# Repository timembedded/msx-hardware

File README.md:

# msx-hardware
MSX hardware related things

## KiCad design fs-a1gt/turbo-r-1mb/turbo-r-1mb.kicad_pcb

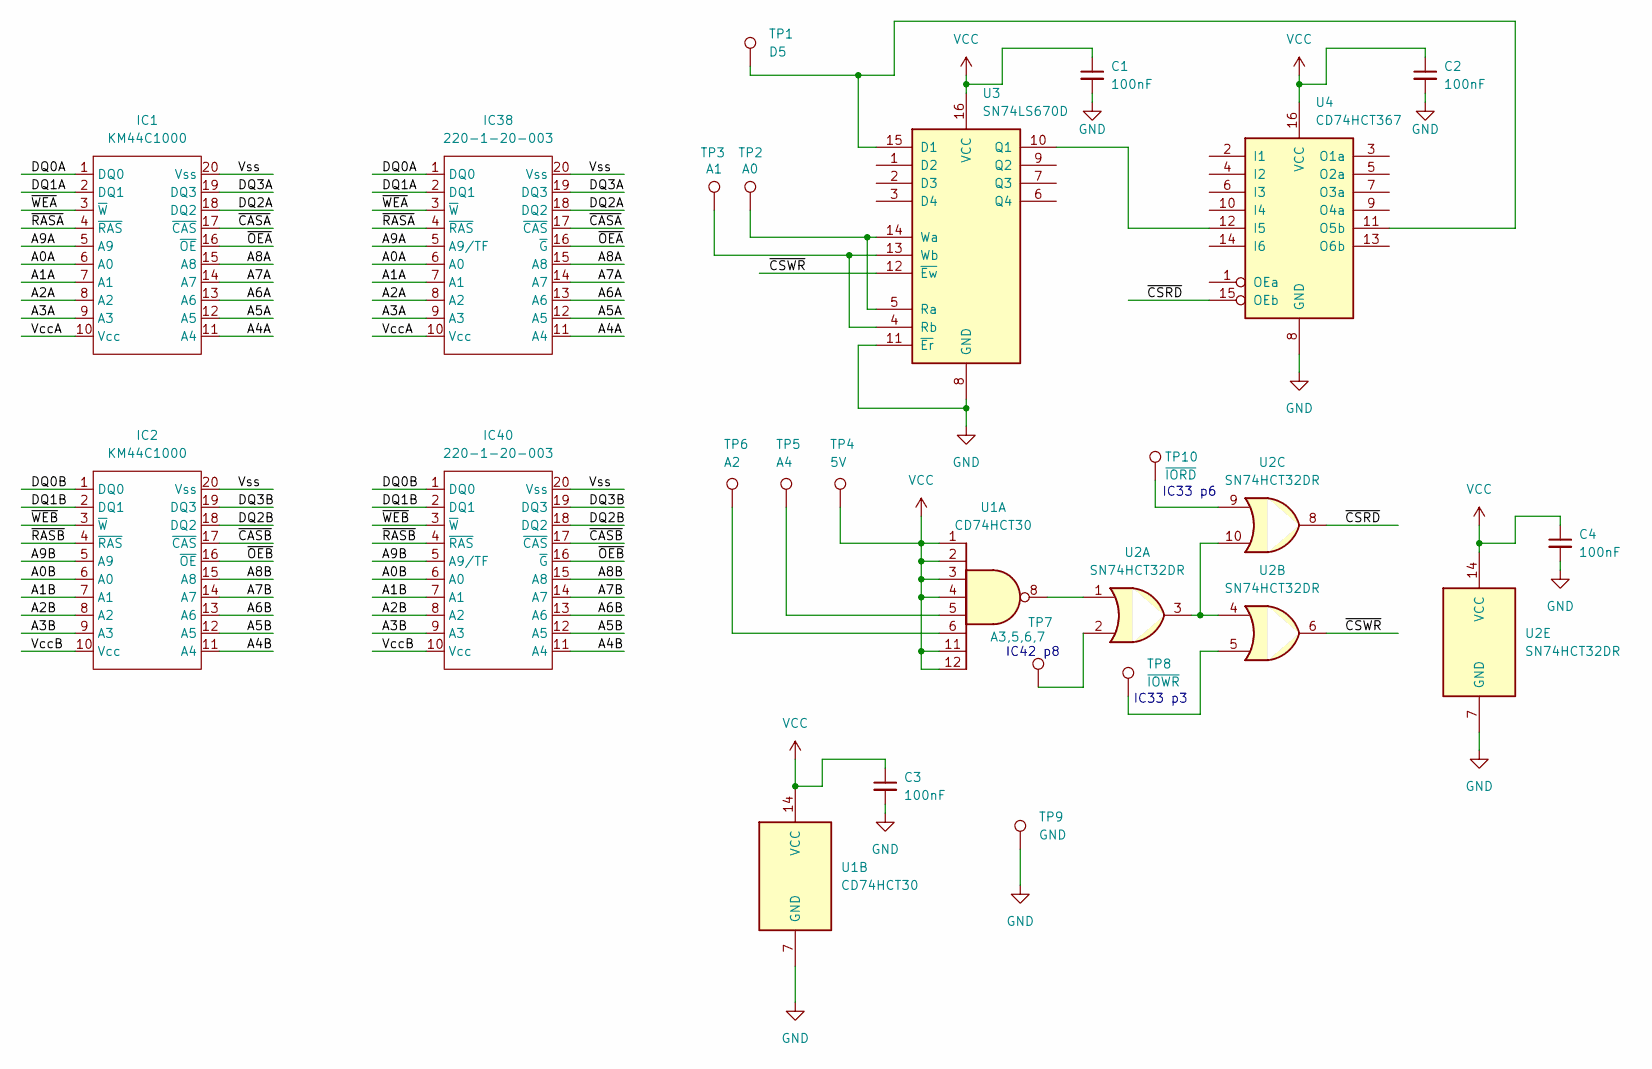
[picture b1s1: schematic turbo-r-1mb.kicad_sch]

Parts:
C1, C2, C3, C4: 100nF; C_0603_1608Metric; DigiKey 311-1088-1-ND
IC1, IC2: KM44C1000; SOJ-20-26_300mil; DigiKey 1175-1523-5-ND
IC38, IC40: 220-1-20-003; DIP-20_W7.62mm_B2B; DigiKey 1175-1523-5-ND
TP1: D5; TestPoint_Pad_D1.5mm
TP2: A0; TestPoint_Pad_D1.5mm
TP3: A1; TestPoint_Pad_D1.5mm
TP4: 5V; TestPoint_Pad_D1.5mm
TP5: A4; TestPoint_Pad_D1.5mm
TP6: A2; TestPoint_Pad_D1.5mm
TP7: A3,5,6,7; TestPoint_Pad_D1.5mm
TP8: ~{IOWR}; TestPoint_Pad_D1.5mm
TP9: GND; TestPoint_Pad_D1.5mm
TP10: ~{IORD}; TestPoint_Pad_D1.5mm
U1: CD74HCT30; SOIC-14_3.9x8.7mm_P1.27mm; DigiKey 296-CD74HCT30M96CT-ND
U2: SN74HCT32DR; SOIC-14_3.9x8.7mm_P1.27mm; DigiKey 296-14868-1-ND
U3: SN74LS670D; SOIC-16_3.9x9.9mm_P1.27mm; DigiKey SN74LS670D-ND
U4: CD74HCT367; SOIC-16_3.9x9.9mm_P1.27mm; DigiKey 296-31612-1-ND

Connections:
/A0A: IC1.6 (A0), IC38.6 (A0)
/A0B: IC2.6 (A0), IC40.6 (A0)
/A1A: IC1.7 (A1), IC38.7 (A1)
/A1B: IC2.7 (A1), IC40.7 (A1)
/A2A: IC1.8 (A2), IC38.8 (A2)
/A2B: IC2.8 (A2), IC40.8 (A2)
/A3A: IC1.9 (A3), IC38.9 (A3)
/A3B: IC2.9 (A3), IC40.9 (A3)
/A4A: IC1.11 (A4), IC38.11 (A4)
/A4B: IC2.11 (A4), IC40.11 (A4)
/A5A: IC1.12 (A5), IC38.12 (A5)
/A5B: IC2.12 (A5), IC40.12 (A5)
/A6A: IC1.13 (A6), IC38.13 (A6)
/A6B: IC2.13 (A6), IC40.13 (A6)
/A7A: IC1.14 (A7), IC38.14 (A7)
/A7B: IC2.14 (A7), IC40.14 (A7)
/A8A: IC1.15 (A8), IC38.15 (A8)
/A8B: IC2.15 (A8), IC40.15 (A8)
/A9A: IC1.5 (A9), IC38.5 (A9/TF)
/A9B: IC2.5 (A9), IC40.5 (A9/TF)
/DQ0A: IC1.1 (DQ0), IC38.1 (DQ0)
/DQ0B: IC2.1 (DQ0), IC40.1 (DQ0)
/DQ1A: IC1.2 (DQ1), IC38.2 (DQ1)
/DQ1B: IC2.2 (DQ1), IC40.2 (DQ1)
/DQ2A: IC1.18 (DQ2), IC38.18 (DQ2)
/DQ2B: IC2.18 (DQ2), IC40.18 (DQ2)
/DQ3A: IC1.19 (DQ3), IC38.19 (DQ3)
/DQ3B: IC2.19 (DQ3), IC40.19 (DQ3)
/VccA: IC1.10 (Vcc), IC38.10 (Vcc)
/VccB: IC2.10 (Vcc), IC40.10 (Vcc)
/Vss: IC1.20 (Vss), IC2.20 (Vss), IC38.20 (Vss), IC40.20 (Vss)
/~CASA: IC1.17 (~CAS), IC38.17 (~CAS)
/~CASB: IC2.17 (~CAS), IC40.17 (~CAS)
/~CSRD: U2.8, U4.15 (OEb)
/~CSWR: U2.6, U3.12 (~Ew)
/~OEA: IC1.16 (~OE), IC38.16 (~G)
/~OEB: IC2.16 (~OE), IC40.16 (~G)
/~RASA: IC1.4 (~RAS), IC38.4 (~RAS)
/~RASB: IC2.4 (~RAS), IC40.4 (~RAS)
/~WEA: IC1.3 (~W), IC38.3 (~W)
/~WEB: IC2.3 (~W), IC40.3 (~W)
GND: C1.2, C2.2, C3.2, C4.2, TP9.1, U1.7 (GND), U2.7 (GND), U3.8 (GND), U3.11 (~Er), U4.8 (GND)
unnamed: TP5.1, U1.5
unnamed: TP6.1, U1.6
unnamed: TP7.1, U2.2
unnamed: TP8.1, U2.5
unnamed: TP10.1, U2.9
unnamed: U1.8, U2.1
unnamed: U2.3, U2.4, U2.10
unnamed: TP1.1, U3.15 (D1), U4.11 (O5b)
unnamed: U3.10 (Q1), U4.12 (I5)
unnamed: TP2.1, U3.5 (Ra), U3.14 (Wa)
unnamed: TP3.1, U3.4 (Rb), U3.13 (Wb)
VCC: C1.1, C2.1, C3.1, C4.1, TP4.1, U1.1, U1.2, U1.3, U1.4, U1.11, U1.12, U1.14 (VCC), U2.14 (VCC), U3.16 (VCC), U4.16 (VCC)

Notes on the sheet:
IC33 p3
IC42 p8
IC33 p6

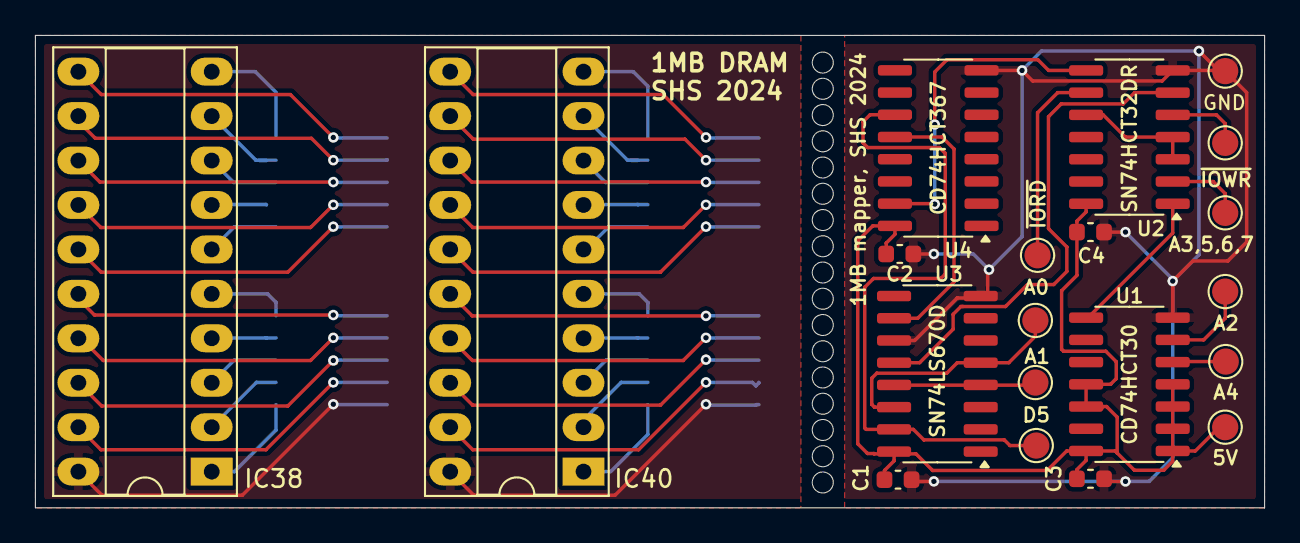
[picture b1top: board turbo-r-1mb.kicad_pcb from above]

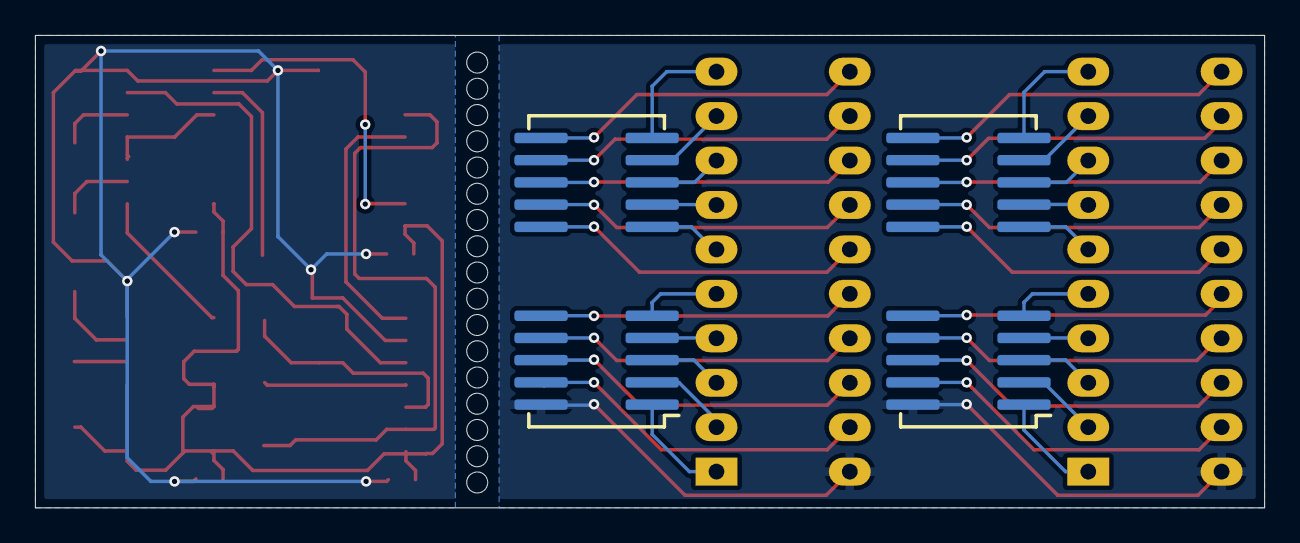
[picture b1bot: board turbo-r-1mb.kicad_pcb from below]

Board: 2 copper layers, 70.2 x 27.0 mm, 22 parts (2 on the bottom side), 54 nets.

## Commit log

2024-09-02 Added pcb design for 1MB memory extension for FS-A1GT
2024-09-03 PCB ready for ordering
